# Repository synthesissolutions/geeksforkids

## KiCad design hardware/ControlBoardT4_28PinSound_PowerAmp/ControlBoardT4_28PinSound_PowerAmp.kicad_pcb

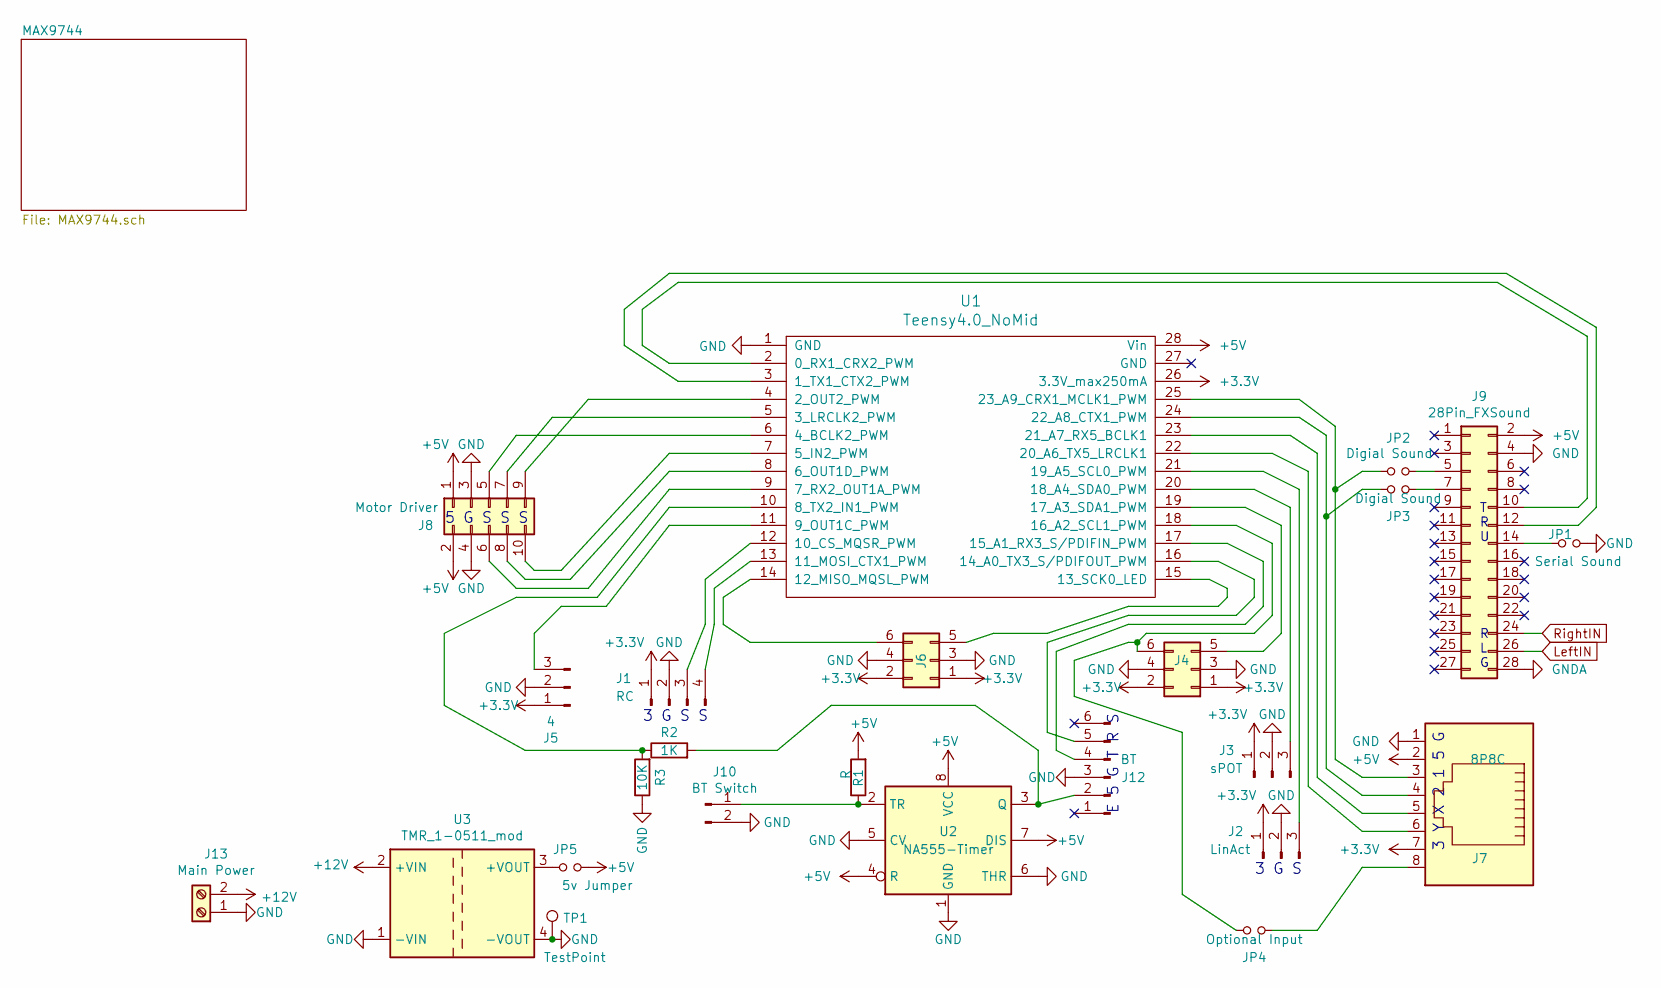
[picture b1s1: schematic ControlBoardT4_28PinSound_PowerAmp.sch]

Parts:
J1: RC; PinHeader_1x04_P2.54mm_Vertical
J2: LinAct; PinHeader_1x03_P2.54mm_Vertical
J3: sPOT; PinHeader_1x03_P2.54mm_Vertical
J4: 1 2; PinHeader_2x03_P2.54mm_Vertical
J5: 4; PinHeader_1x03_P2.54mm_Vertical
J6: 5 6; PinHeader_2x03_P2.54mm_Vertical
J7: 8P8C; RJ45_x08_Horizontal_tabs
J8: Motor Driver; PinHeader_2x05_P2.54mm_Vertical
J9: 28Pin_FXSound; FXSound_HeadPhone_2x14_P2.54mm_Short
J10: BT Switch; PinHeader_1x02_P2.54mm_Vertical
J12: BT; PinHeader_1x06_P2.54mm_Vertical
J13: Main Power; TerminalBlock_bornier-2_P5.08mm
JP1: Serial Sound; SolderJumper-2_P1.3mm_Open_TrianglePad1.0x1.5mm
JP2, JP3: Digial Sound; SolderJumper-2_P1.3mm_Open_TrianglePad1.0x1.5mm
JP4: Optional Input; SolderJumper-2_P1.3mm_Open_TrianglePad1.0x1.5mm
JP5: 5v Jumper; SolderJumper-2_P1.3mm_Open_TrianglePad1.0x1.5mm
R1: R; R_0805_2012Metric_Pad1.15x1.40mm_HandSolder
R2: 1K; R_0805_2012Metric_Pad1.15x1.40mm_HandSolder
R3: 10K; R_0805_2012Metric_Pad1.15x1.40mm_HandSolder; DigiKey ID RNCP0805FTD10K0CT-ND
TP1: TestPoint; TestPoint_Pad_1.5x1.5mm
U1: Teensy4.0_NoMid; Teensy40_NoMid
U2: NA555-Timer; DIP-8_W7.62mm
U3: TMR_1-0511_mod; Regulator_LM2596Adj

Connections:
+3V3: J1.1, J2.1, J3.1, J4.1, J4.2, J5.1, J6.1, J6.2, J7.7, U1.26 (3.3V_max250mA); also elsewhere on the board
+5V: J7.2, J8.1, J8.2, J9.2, JP5.2, R1.2, U1.28 (Vin), U2.4 (R), U2.7 (DIS), U2.8 (VCC)
+12V: J13.2, U3.2 (+VIN); also elsewhere on the board
GND: J1.2, J2.2, J3.2, J4.3, J4.4, J5.2, J6.3, J6.4, J7.1, J8.3, J8.4, J9.4, J10.2, J12.3, J13.1, JP1.2, R3.1, TP1.1, U1.1 (GND), U2.1 (GND), U2.5 (CV), U2.6 (THR), U3.1 (-VIN), U3.4 (-VOUT); also elsewhere on the board
GNDA: J9.28; also elsewhere on the board
LeftIN: J9.26; also elsewhere on the board
unnamed: J1.3, U1.12 (10_CS_MQSR_PWM)
unnamed: J1.4, U1.13 (11_MOSI_CTX1_PWM)
unnamed: J2.3, U1.21 (19_A5_SCL0_PWM)
unnamed: J3.3, U1.20 (18_A4_SDA0_PWM)
unnamed: J4.5, U1.19 (17_A3_SDA1_PWM)
unnamed: J4.6, JP4.1, U1.18 (16_A2_SCL1_PWM)
unnamed: J5.3, U1.11 (9_OUT1C_PWM)
unnamed: J6.5, U1.15 (13_SCK0_LED)
unnamed: J6.6, U1.14 (12_MISO_MQSL_PWM)
unnamed: J7.3, JP2.1, U1.25 (23_A9_CRX1_MCLK1_PWM)
unnamed: J7.4, JP3.1, U1.24 (22_A8_CTX1_PWM)
unnamed: J7.5, U1.23 (21_A7_RX5_BCLK1)
unnamed: J7.6, U1.22 (20_A6_TX5_LRCLK1)
unnamed: J7.8, JP4.2
unnamed: J8.5, U1.6 (4_BCLK2_PWM)
unnamed: J8.6, U1.9 (7_RX2_OUT1A_PWM)
unnamed: J8.7, U1.5 (3_LRCLK2_PWM)
unnamed: J8.8, U1.8 (6_OUT1D_PWM)
unnamed: J8.9, U1.4 (2_OUT2_PWM)
unnamed: J8.10, U1.7 (5_IN2_PWM)
unnamed: J9.5, JP2.2
unnamed: J9.7, JP3.2
unnamed: J9.10, U1.2 (0_RX1_CRX2_PWM)
unnamed: J9.12, U1.3 (1_TX1_CTX2_PWM)
unnamed: J9.14, JP1.1
unnamed: J10.1, R1.1, U2.2 (TR)
unnamed: J12.2, R2.2, U2.3 (Q)
unnamed: J12.4, U1.17 (15_A1_RX3_S/PDIFIN_PWM)
unnamed: J12.5, U1.16 (14_A0_TX3_S/PDIFOUT_PWM)
unnamed: JP5.1, U3.3 (+VOUT)
unnamed: R2.1, R3.2, U1.10 (8_TX2_IN1_PWM)
RightIN: J9.24; also elsewhere on the board

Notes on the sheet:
3 Y X 2 1 5 G
3 G S S
5 G S S S
3 G S
T R U
R L G
E 5 G T R S

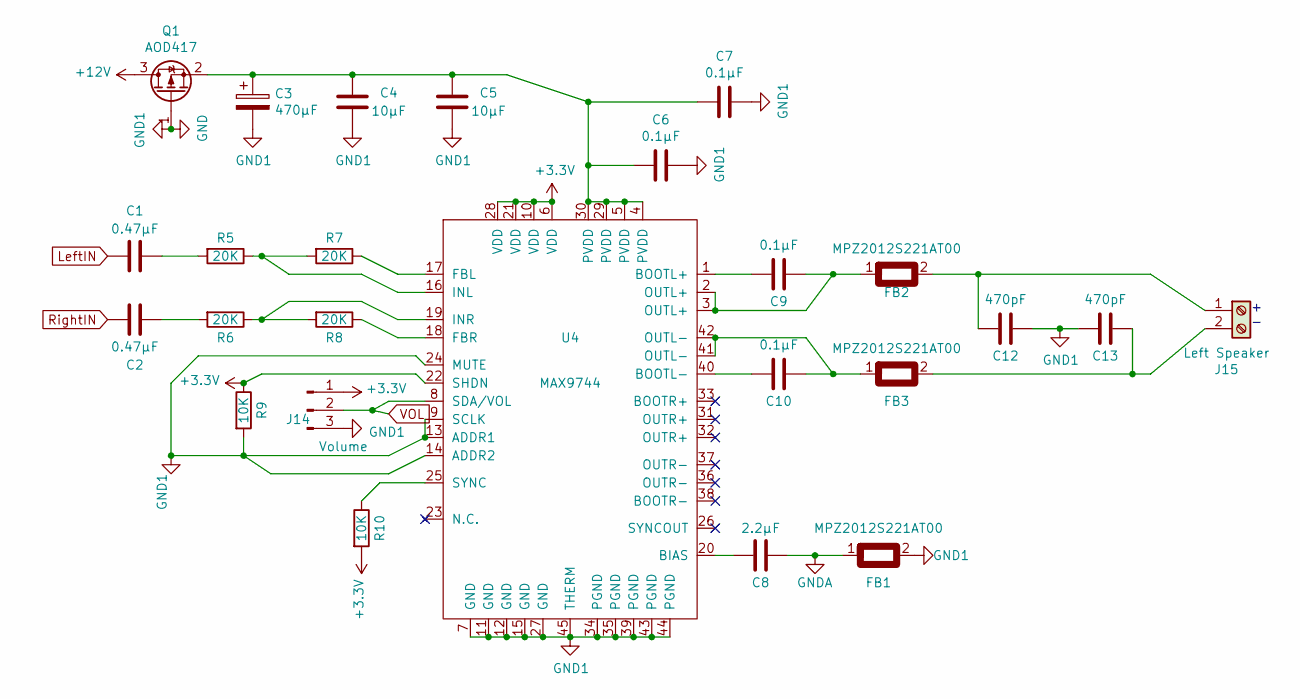
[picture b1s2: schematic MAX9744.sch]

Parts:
C1, C2: 0.47µF; C_0805_2012Metric_Pad1.15x1.40mm_HandSolder; DigiKey ID 399-8099-1-ND
C3: 470µF; CP_Radial_D8.0mm_P3.50mm; DigiKey ID 1189-1859-ND
C4, C5: 10µF; C_0805_2012Metric_Pad1.15x1.40mm_HandSolder; DigiKey ID 399-8012-1-ND
C6, C7, C9, C10: 0.1µF; C_0805_2012Metric_Pad1.15x1.40mm_HandSolder; DigiKey ID 399-8000-1-ND
C8: 2.2µF; C_0805_2012Metric_Pad1.15x1.40mm_HandSolder; DigiKey ID 399-11941-1-ND
C12, C13: 470pF; C_0805_2012Metric_Pad1.15x1.40mm_HandSolder; DigiKey ID 399-1142-1-ND
FB1, FB2, FB3: MPZ2012S221AT00; L_0805_2012Metric_Pad1.15x1.40mm_HandSolder; DigiKey ID 445-1568-1-ND
J14: Volume; JST_XH_B3B-XH-A_1x03_P2.54mm_Vertical
J15: Left Speaker; TerminalBlock_bornier-2_P5.08mm
Q1: AOD417; TO-252-2pin3D; DigiKey ID 785-1106-1-ND
R5, R6, R7, R8: 20K; R_0805_2012Metric_Pad1.15x1.40mm_HandSolder; DigiKey ID 311-20.0KCRCT-ND
R9, R10: 10K; R_0805_2012Metric_Pad1.15x1.40mm_HandSolder; DigiKey ID RNCP0805FTD10K0CT-ND
U4: MAX9744; max9744eth&plus_Mod; DigiKey ID MAX9744ETH+-ND

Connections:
+3V3: J14.1, R9.1, R10.2, U4.6 (VDD), U4.10 (VDD), U4.21 (VDD), U4.22 (SHDN), U4.28 (VDD); also elsewhere on the board
+12V: Q1.3 (D); also elsewhere on the board
GND: C3.2, C4.1, C5.1, C6.1, C7.1, C12.1, C13.2, FB1.2, J14.3, Q1.1 (G), R9.2, U4.7 (GND), U4.9 (SCLK), U4.11 (GND), U4.12 (GND), U4.13 (ADDR1), U4.14 (ADDR2), U4.15 (GND), U4.24 (MUTE), U4.27 (GND), U4.34 (PGND), U4.35 (PGND), U4.39 (PGND), U4.43 (PGND), U4.44 (PGND), U4.45 (THERM); also elsewhere on the board
GNDA: C8.2, FB1.1; also elsewhere on the board
LeftIN: C1.2; also elsewhere on the board
unnamed: C1.1, R5.2
unnamed: C2.1, R6.2
unnamed: C3.1, C4.2, C5.2, C6.2, C7.2, Q1.2 (S), U4.4 (PVDD), U4.5 (PVDD), U4.29 (PVDD), U4.30 (PVDD)
unnamed: C8.1, U4.20 (BIAS)
unnamed: C9.1, FB2.1, U4.2 (OUTL+), U4.3 (OUTL+)
unnamed: C9.2, U4.1 (BOOTL+)
unnamed: C10.1, FB3.1, U4.41 (OUTL-), U4.42 (OUTL-)
unnamed: C10.2, U4.40 (BOOTL-)
unnamed: C12.2, FB2.2, J15.1
unnamed: C13.1, FB3.2, J15.2
unnamed: J14.2, U4.8 (SDA/VOL)
unnamed: R5.1, R7.2, U4.16 (INL)
unnamed: R6.1, R8.2, U4.19 (INR)
unnamed: R7.1, U4.17 (FBL)
unnamed: R8.1, U4.18 (FBR)
unnamed: R10.1, U4.25 (SYNC)
RightIN: C2.2; also elsewhere on the board

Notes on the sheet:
+ -

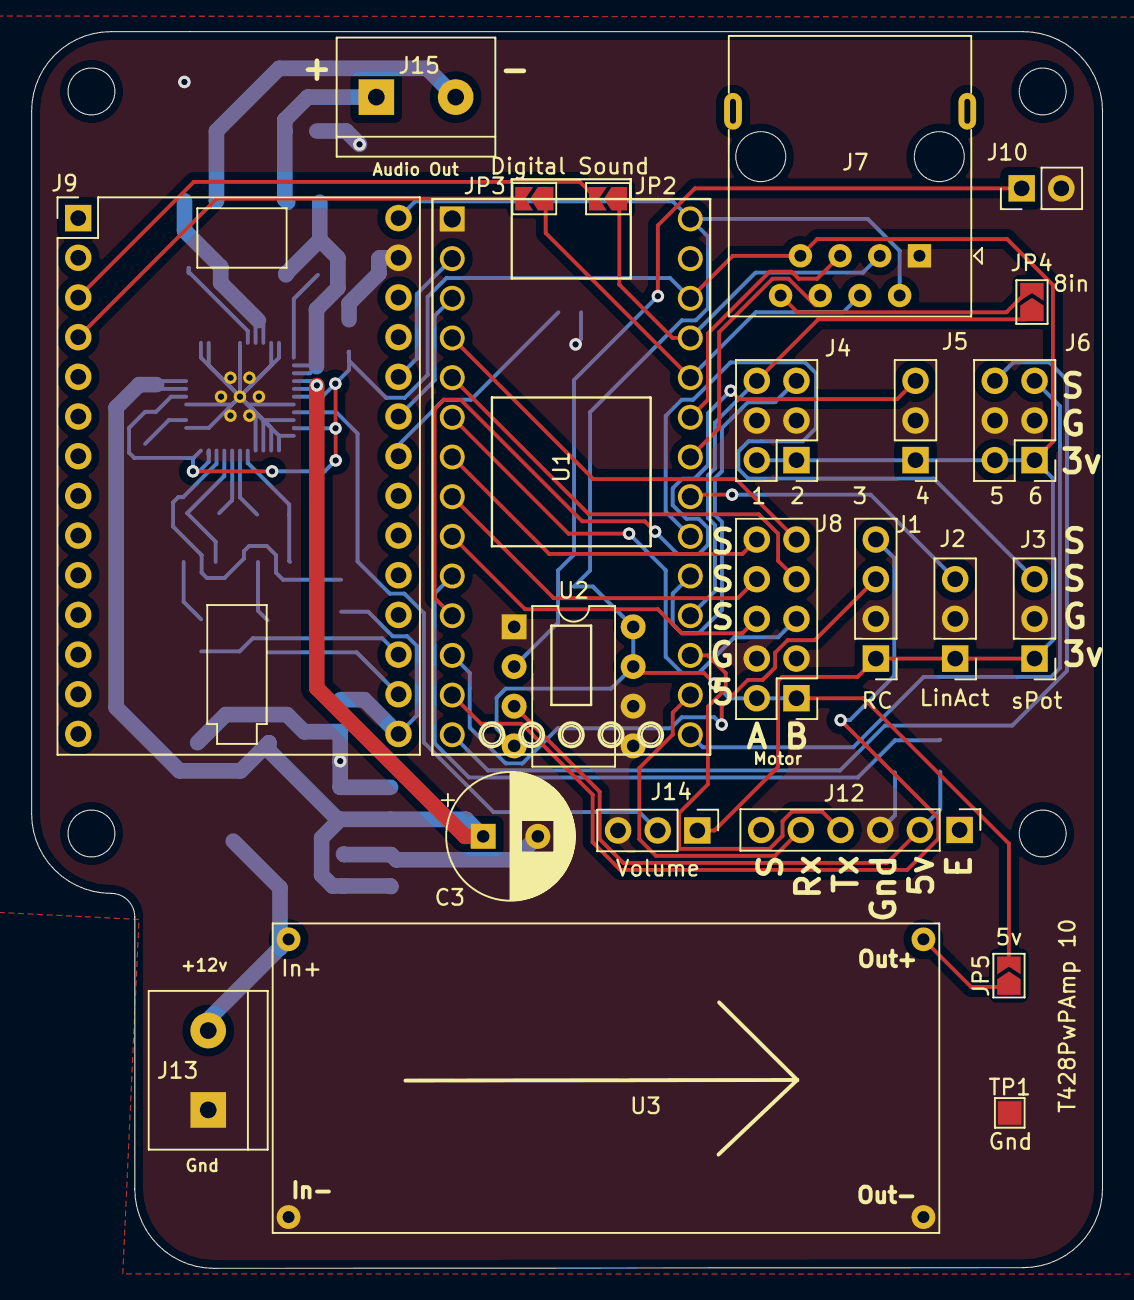
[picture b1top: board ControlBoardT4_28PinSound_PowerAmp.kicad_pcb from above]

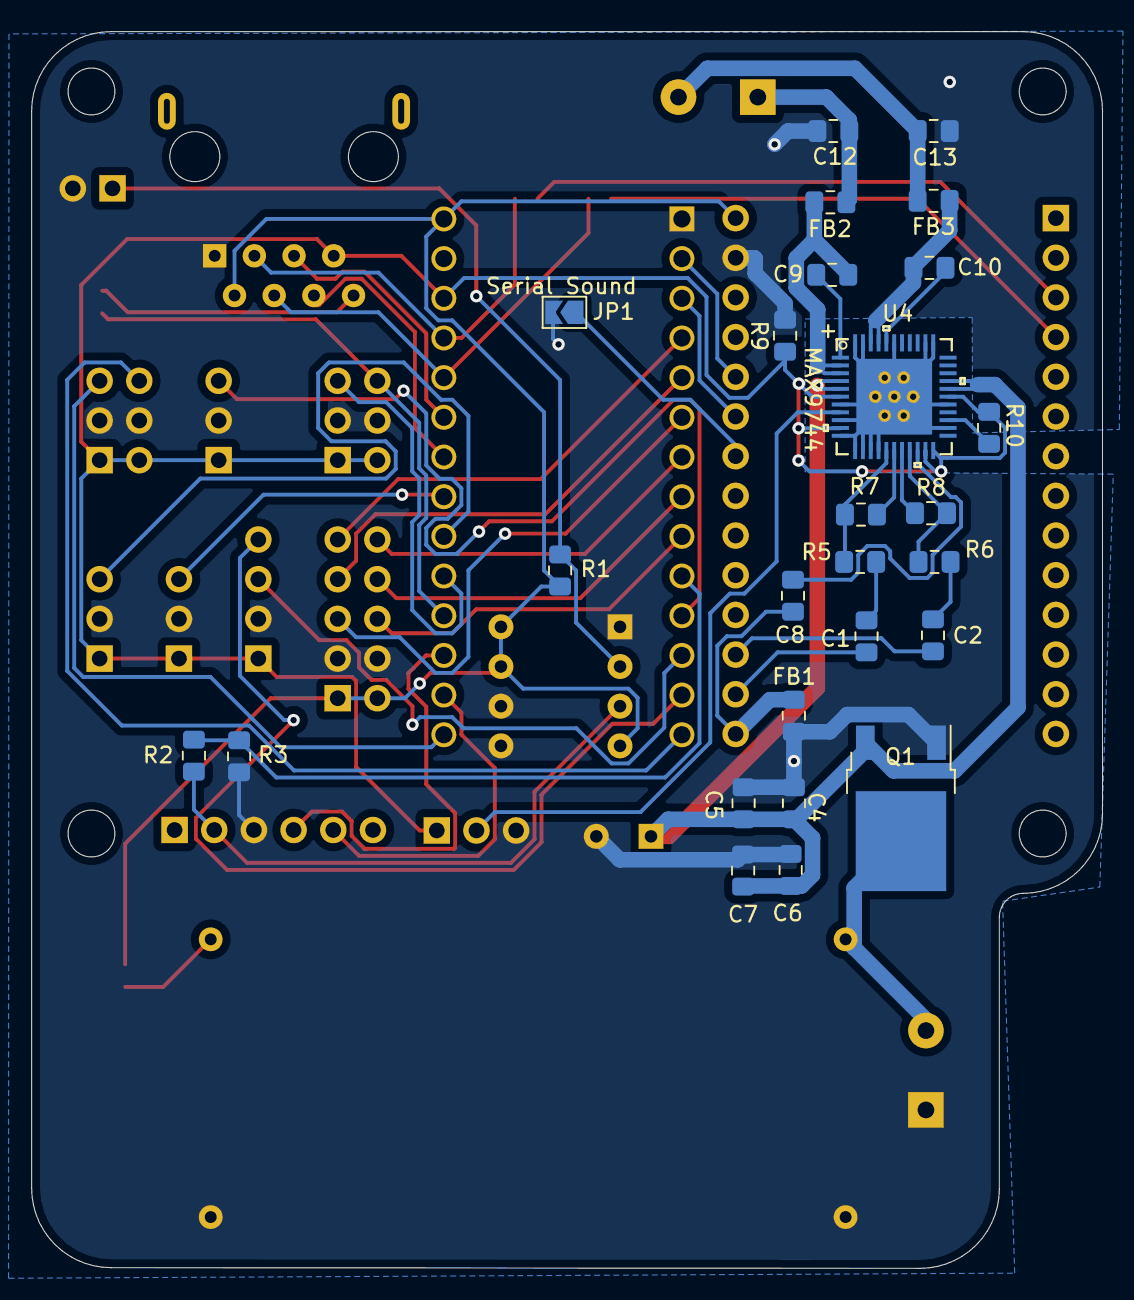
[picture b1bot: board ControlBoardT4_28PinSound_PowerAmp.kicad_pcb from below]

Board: 2 copper layers, 68.6 x 79.2 mm, 49 parts (26 on the bottom side), 54 nets.

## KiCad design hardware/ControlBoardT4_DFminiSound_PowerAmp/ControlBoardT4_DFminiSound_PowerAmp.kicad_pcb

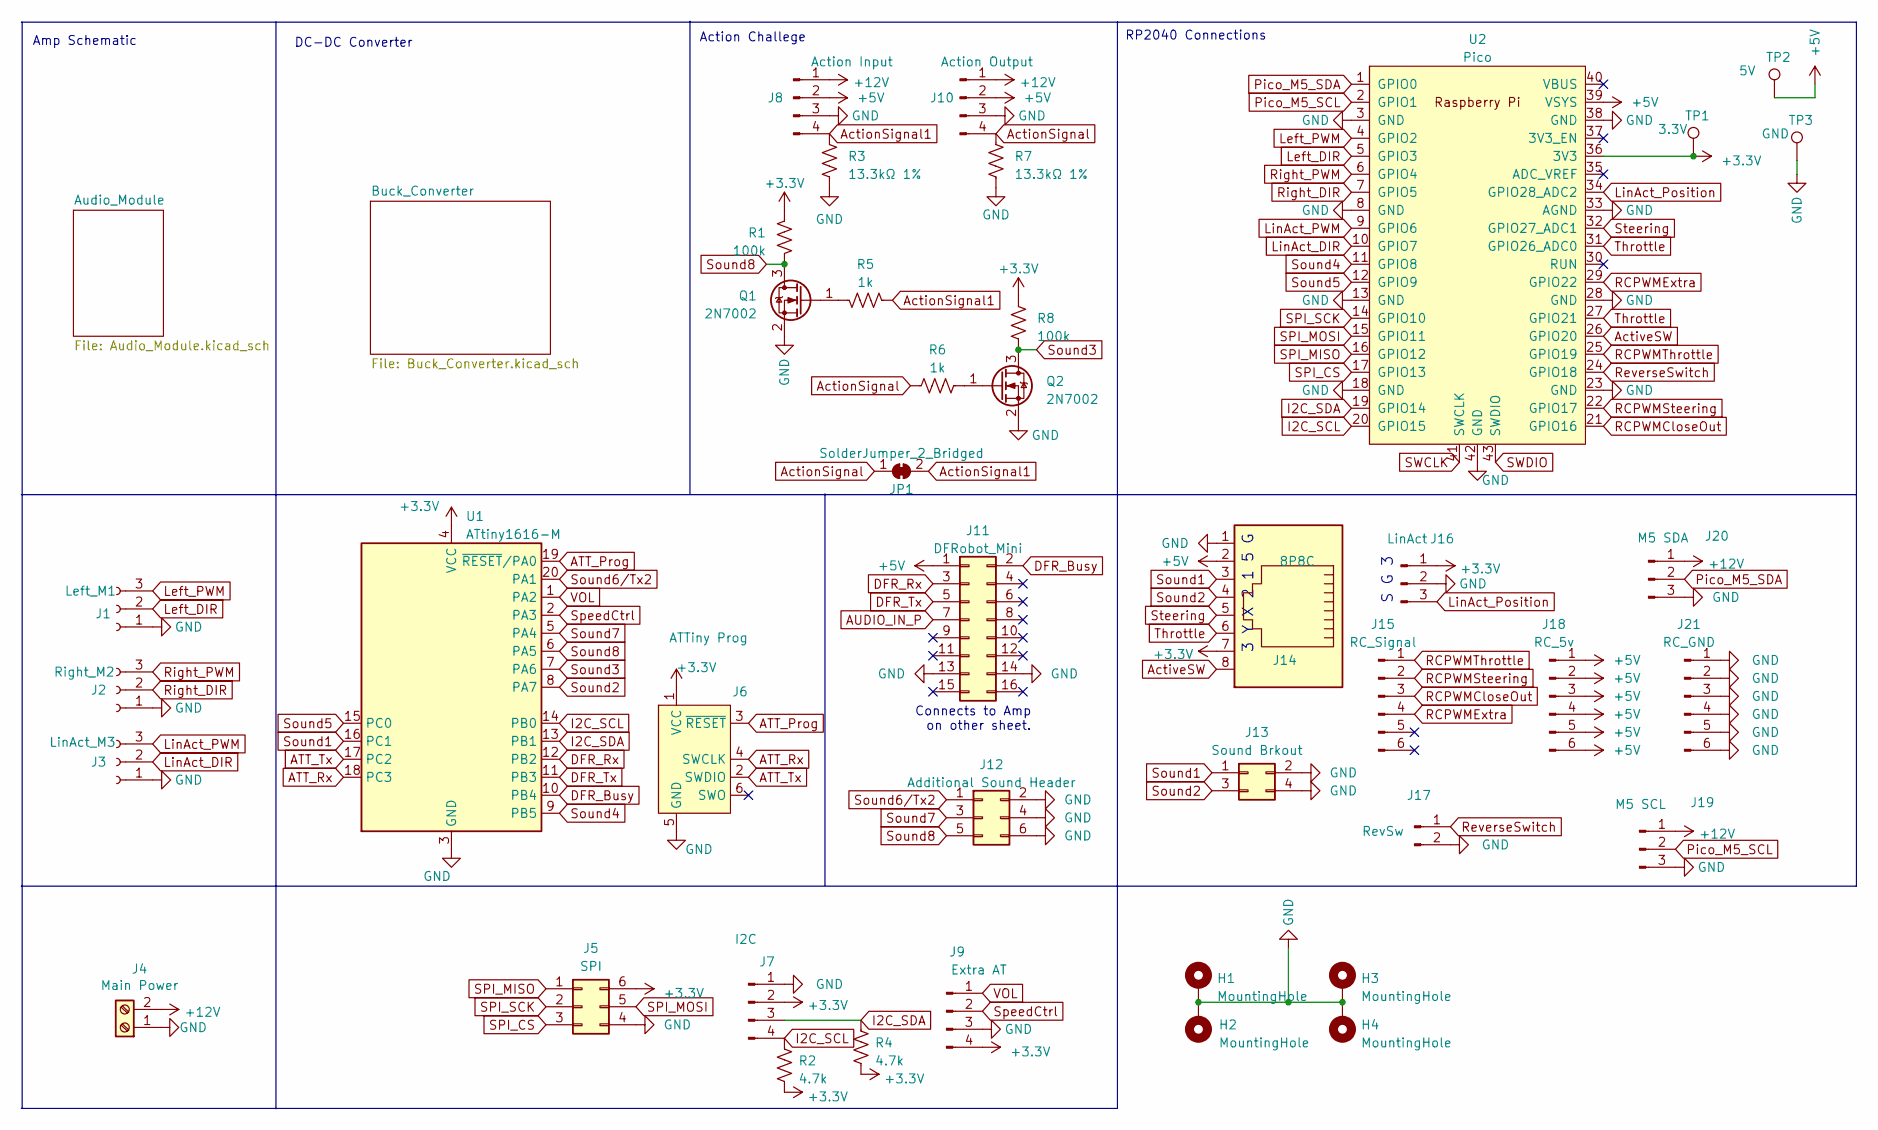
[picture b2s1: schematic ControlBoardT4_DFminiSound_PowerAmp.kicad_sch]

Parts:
H1, H2, H3, H4: MountingHole; MountingHole_2.7mm_M2.5_Pad
J1: Left_M1; PinHeader_1x03_P2.54mm_Vertical
J2: Right_M2; PinHeader_1x03_P2.54mm_Vertical
J3: LinAct_M3; PinHeader_1x03_P2.54mm_Vertical
J4: Main Power; TerminalBlock_bornier-2_P5.08mm
J5: SPI; PinHeader_2x03_P2.54mm_Vertical
J6: ATTiny Prog; Tag-Connect_TC2030-IDC-NL_2x03_P1.27mm_Vertical
J7: I2C; PinHeader_1x04_P2.54mm_Vertical
J8: Action Input; JST_XH_B4B-XH-A_1x04_P2.50mm_Vertical
J9: Extra AT; PinHeader_1x04_P2.54mm_Vertical
J10: Action Output; JST_XH_B4B-XH-A_1x04_P2.50mm_Vertical
J11: DFRobot_Mini; DFRobotMini_2x08_P2.54mm_Vertical
J12: Additional Sound Header; PinSocket_2x03_P2.54mm_Vertical
J13: Sound Brkout; PinSocket_2x02_P2.54mm_Vertical
J14: 8P8C; RJ45_x08_Tab_Up
J15: RC_Signal; PinSocket_1x06_P2.54mm_Vertical
J16: LinAct; JST_XH_B3B-XH-A_1x03_P2.54mm_Vertical
J17: RevSw; JST_XH_B2B-XH-A_1x02_P2.50mm_Vertical
J18: RC_5v; PinSocket_1x06_P2.54mm_Vertical
J19: M5 SCL; JST_XH_B3B-XH-A_1x03_P2.54mm_Vertical
J20: M5 SDA; JST_XH_B3B-XH-A_1x03_P2.54mm_Vertical
J21: RC_GND; PinSocket_1x06_P2.54mm_Vertical
JP1: SolderJumper_2_Bridged; SolderJumper-2_P1.3mm_Bridged_RoundedPad1.0x1.5mm
Q1, Q2: 2N7002; SOT-23; MPN C8545
R1, R8: 100k; R_0402_1005Metric; MPN C60491
R2, R4: 4.7k; R_0402_1005Metric; MPN C25900
R3, R7: 13.3kΩ 1%; R_0603_1608Metric; MPN C25952
R5, R6: 1k; R_0402_1005Metric; MPN C11702
TP1: 3.3V; TestPoint_Pad_1.5x1.5mm
TP2: 5V; TestPoint_Pad_1.5x1.5mm
TP3: GND; TestPoint_Pad_1.5x1.5mm
U1: ATtiny1616-M; VQFN-20-1EP_3x3mm_P0.4mm_EP1.7x1.7mm; MPN C507118
U2: Pico; RPi_Pico_SMD_TH

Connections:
+3.3V: J5.6, J6.1 (VCC), J7.2, J9.4, J14.7, J16.1, R1.1, R2.1, R4.1, R8.1, TP1.1, U1.4 (VCC), U2.36 (3V3)
+5V: J8.2, J10.2, J11.1, J14.2, J18.1, J18.2, J18.3, J18.4, J18.5, J18.6, TP2.1, U2.39 (VSYS); also elsewhere on the board
+12V: J4.2, J8.1, J10.1, J19.1, J20.1; also elsewhere on the board
ATT_Prog: J6.3 (~RESET), U1.19 (~RESET/PA0)
ATT_Rx: J6.4 (SWCLK), U1.18 (PC3)
ATT_Tx: J6.2 (SWDIO), U1.17 (PC2)
AUDIO_IN_P: J11.7; also elsewhere on the board
ActionSignal: J10.4, JP1.1 (A), R6.1, R7.1
ActionSignal1: J8.4, JP1.2 (B), R3.1, R5.1
ActiveSW: J14.8, U2.26 (GPIO20)
DFR_Busy: J11.2, U1.10 (PB4)
DFR_Rx: J11.3, U1.12 (PB2)
DFR_Tx: J11.5, U1.11 (PB3)
GND: H1.1, H2.1, H3.1, H4.1, J1.1, J2.1, J3.1, J4.1, J5.4, J6.5 (GND), J7.1, J8.3, J9.3, J10.3, J11.13, J11.14, J12.2, J12.4, J12.6, J13.2, J13.4, J14.1, J16.2, J17.2, J19.3, J20.3, J21.1, J21.2, J21.3, J21.4, J21.5, J21.6, Q1.2 (S), Q2.2 (S), R3.2, R7.2, TP3.1, U1.3 (GND), U1.21 (GND), U2.3 (GND), U2.8 (GND), U2.13 (GND), U2.18 (GND), U2.23 (GND), U2.28 (GND), U2.33 (AGND), U2.38 (GND), U2.42 (GND); also elsewhere on the board
I2C_SCL: J7.4, R2.2, U1.14 (PB0), U2.20 (GPIO15)
I2C_SDA: J7.3, R4.2, U1.13 (PB1), U2.19 (GPIO14)
Left_DIR: J1.2, U2.5 (GPIO3)
Left_PWM: J1.3, U2.4 (GPIO2)
LinAct_DIR: J3.2, U2.10 (GPIO7)
LinAct_PWM: J3.3, U2.9 (GPIO6)
LinAct_Position: J16.3, U2.34 (GPIO28_ADC2)
unnamed: Q1.1 (G), R5.2
unnamed: Q2.1 (G), R6.2
Pico_M5_SCL: J19.2, U2.2 (GPIO1)
Pico_M5_SDA: J20.2, U2.1 (GPIO0)
RCPWMCloseOut: J15.3, U2.21 (GPIO16)
RCPWMExtra: J15.4, U2.29 (GPIO22)
RCPWMSteering: J15.2, U2.22 (GPIO17)
RCPWMThrottle: J15.1, U2.25 (GPIO19)
ReverseSwitch: J17.1, U2.24 (GPIO18)
Right_DIR: J2.2, U2.7 (GPIO5)
Right_PWM: J2.3, U2.6 (GPIO4)
SPI_CS: J5.3, U2.17 (GPIO13)
SPI_MISO: J5.1, U2.16 (GPIO12)
SPI_MOSI: J5.5, U2.15 (GPIO11)
SPI_SCK: J5.2, U2.14 (GPIO10)
SWCLK: U2.41 (SWCLK)
SWDIO: U2.43 (SWDIO)
Sound1: J13.1, J14.3, U1.16 (PC1)
Sound2: J13.3, J14.4, U1.8 (PA7)
Sound3: Q2.3 (D), R8.2, U1.7 (PA6)
Sound4: U1.9 (PB5), U2.11 (GPIO8)
Sound5: U1.15 (PC0), U2.12 (GPIO9)
Sound6/Tx2: J12.1, U1.20 (PA1)
Sound7: J12.3, U1.5 (PA4)
Sound8: J12.5, Q1.3 (D), R1.2, U1.6 (PA5)
SpeedCtrl: J9.2, U1.2 (PA3)
Steering: J14.5, U2.32 (GPIO27_ADC1)
Throttle: J14.6, U2.27 (GPIO21), U2.31 (GPIO26_ADC0)
VOL: J9.1, U1.1 (PA2)

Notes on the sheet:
Connects to Amp on other sheet.
3 Y X 2 1 5 G
RP2040 Connections
Amp Schematic
DC-DC Converter
Action Challege
S G 3

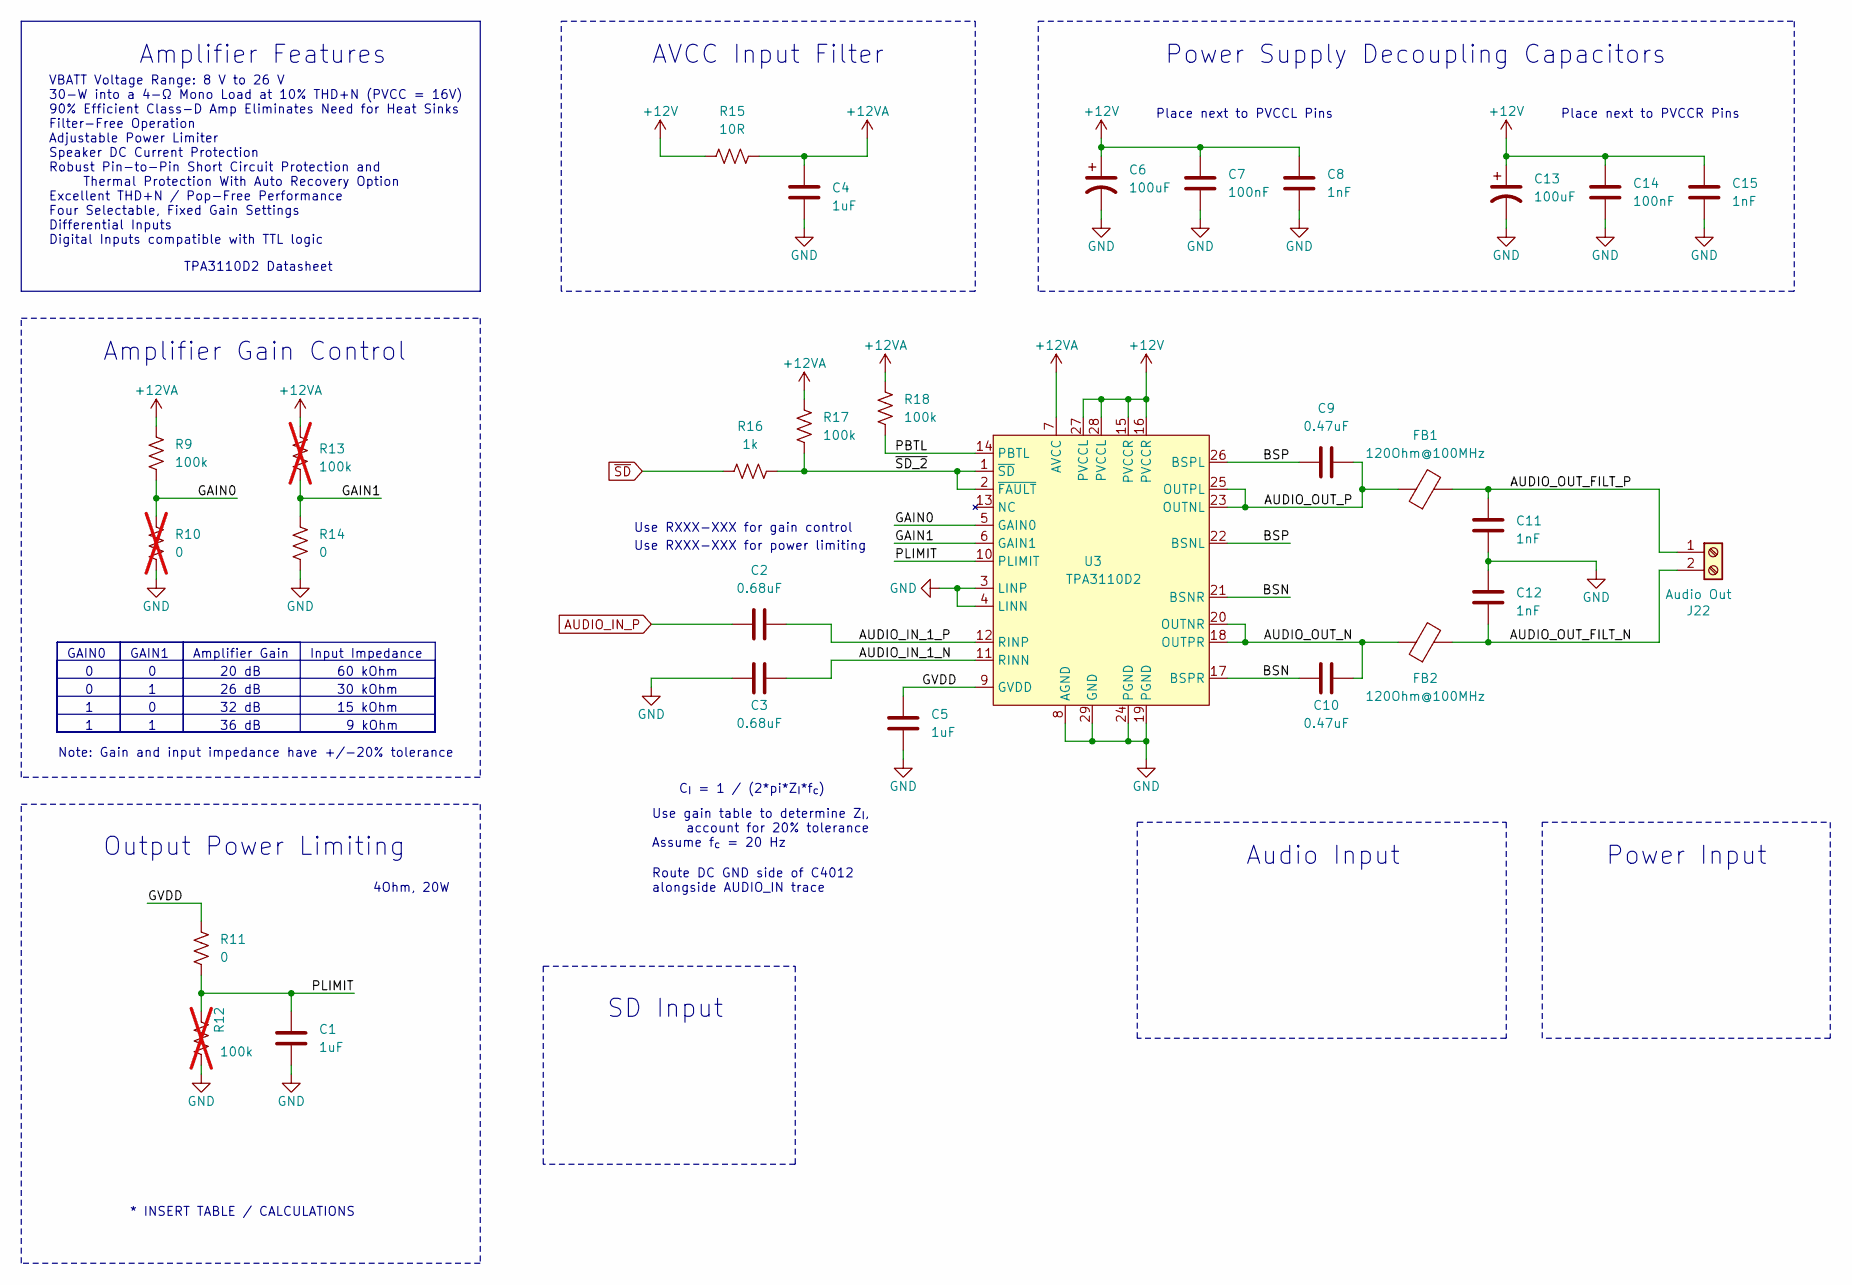
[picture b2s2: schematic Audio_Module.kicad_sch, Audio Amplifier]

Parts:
C1, C4, C5: 1uF; C_0402_1005Metric; MPN C1518208
C2, C3: 0.68uF; C_0402_1005Metric; MPN C113784
C6, C13: 100uF; CP_Radial_D8.0mm_P3.50mm; MPN C112510
C7, C14: 100nF; C_0402_1005Metric; MPN C105882
C8, C11, C12, C15: 1nF; C_0402_1005Metric; MPN C106205
C9, C10: 0.47uF; C_0402_1005Metric; MPN C437527
FB1, FB2: 120Ohm@100MHz; L_1206_3216Metric; MPN C3011219
J22: Audio Out; TerminalBlock_bornier-2_P5.08mm
R9, R17, R18: 100k; R_0402_1005Metric; MPN C60491
R10: 0; R_0402_1005Metric; MPN C17168; not fitted
R11, R14: 0; R_0402_1005Metric; MPN C17168
R12, R13: 100k; R_0402_1005Metric; MPN C60491; not fitted
R15: 10R; R_0603_1608Metric; MPN C22859
R16: 1k; R_0402_1005Metric; MPN C11702
U3: TPA3110D2; HTSSOP-28-1EP_4.4x9.7mm_P0.65mm_EP3.4x9.5mm_Mask2.4x6.17mm_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; MPN C30132

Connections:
+12V: C6.1, C7.1, C8.1, C13.1, C14.1, C15.1, R15.1, U3.15 (PVCCR), U3.16 (PVCCR), U3.27 (PVCCL), U3.28 (PVCCL); also elsewhere on the board
+12VA: C4.1, R9.1, R13.1, R15.2, R17.1, R18.1, U3.7 (AVCC)
/Audio_Module/AUDIO_IN_1_N: C3.1, U3.11 (RINN)
/Audio_Module/AUDIO_IN_1_P: C2.2, U3.12 (RINP)
/Audio_Module/AUDIO_OUT_FILT_N: C12.2, FB2.2, J22.2
/Audio_Module/AUDIO_OUT_FILT_P: C11.1, FB1.2, J22.1
/Audio_Module/AUDIO_OUT_N: C10.1, FB2.1, U3.18 (OUTPR), U3.20 (OUTNR)
/Audio_Module/AUDIO_OUT_P: C9.1, FB1.1, U3.23 (OUTNL), U3.25 (OUTPL)
/Audio_Module/BSN: C10.2, U3.17 (BSPR), U3.21 (BSNR)
/Audio_Module/BSP: C9.2, U3.22 (BSNL), U3.26 (BSPL)
/Audio_Module/GAIN0: R9.2, R10.1, U3.5 (GAIN0)
/Audio_Module/GAIN1: R13.2, R14.1, U3.6 (GAIN1)
/Audio_Module/GVDD: C5.1, R11.1, U3.9 (GVDD)
/Audio_Module/PBTL: R18.2, U3.14 (PBTL)
/Audio_Module/PLIMIT: C1.1, R11.2, R12.1, U3.10 (PLIMIT)
/Audio_Module/~SD_2: R16.2, R17.2, U3.1 (~SD), U3.2 (~FAULT)
AUDIO_IN_P: C2.1; also elsewhere on the board
GND: C1.2, C3.2, C4.2, C5.2, C6.2, C7.2, C8.2, C11.2, C12.1, C13.2, C14.2, C15.2, R10.2, R12.2, R14.2, U3.3 (LINP), U3.4 (LINN), U3.8 (AGND), U3.19 (PGND), U3.24 (PGND), U3.29 (GND); also elsewhere on the board
~SD: R16.1

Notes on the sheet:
30 kOhm
Route DC GND side of C4012 alongside AUDIO_IN trace
Use gain table to determine Z_{I}, account for 20% tolerance Assume f_{c} = 20 Hz
Use RXXX-XXX for power limiting
Amplifier Gain Control
GAIN0
Output Power Limiting
32 dB
C_{I} = 1 / (2*pi*Z_{I}*f_{c})
Use RXXX-XXX for gain control
20 dB
* INSERT TABLE / CALCULATIONS
SD Input
Audio Input
Note: Gain and input impedance have +/-20% tolerance
26 dB
VBATT Voltage Range: 8 V to 26 V 30-W into a 4-Ω Mono Load at 10% THD+N (PVCC = 16V) 90% Efficient Class-D Amp Eliminates Need for Heat Sinks Filter-Free Operation Adjustable Power Limiter Speaker DC Current Protection Robust Pin-to-Pin Short Circuit Protection and Thermal Protection With Auto Reco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
Amplifier Features
Amplifier Gain
Power Input
36 dB
4Ohm, 20W
TPA3110D2 Datasheet
AVCC Input Filter
15 kOhm
9 kOhm
Place next to PVCCR Pins
GAIN1
60 kOhm
Input Impedance
Power Supply Decoupling Capacitors
Place next to PVCCL Pins

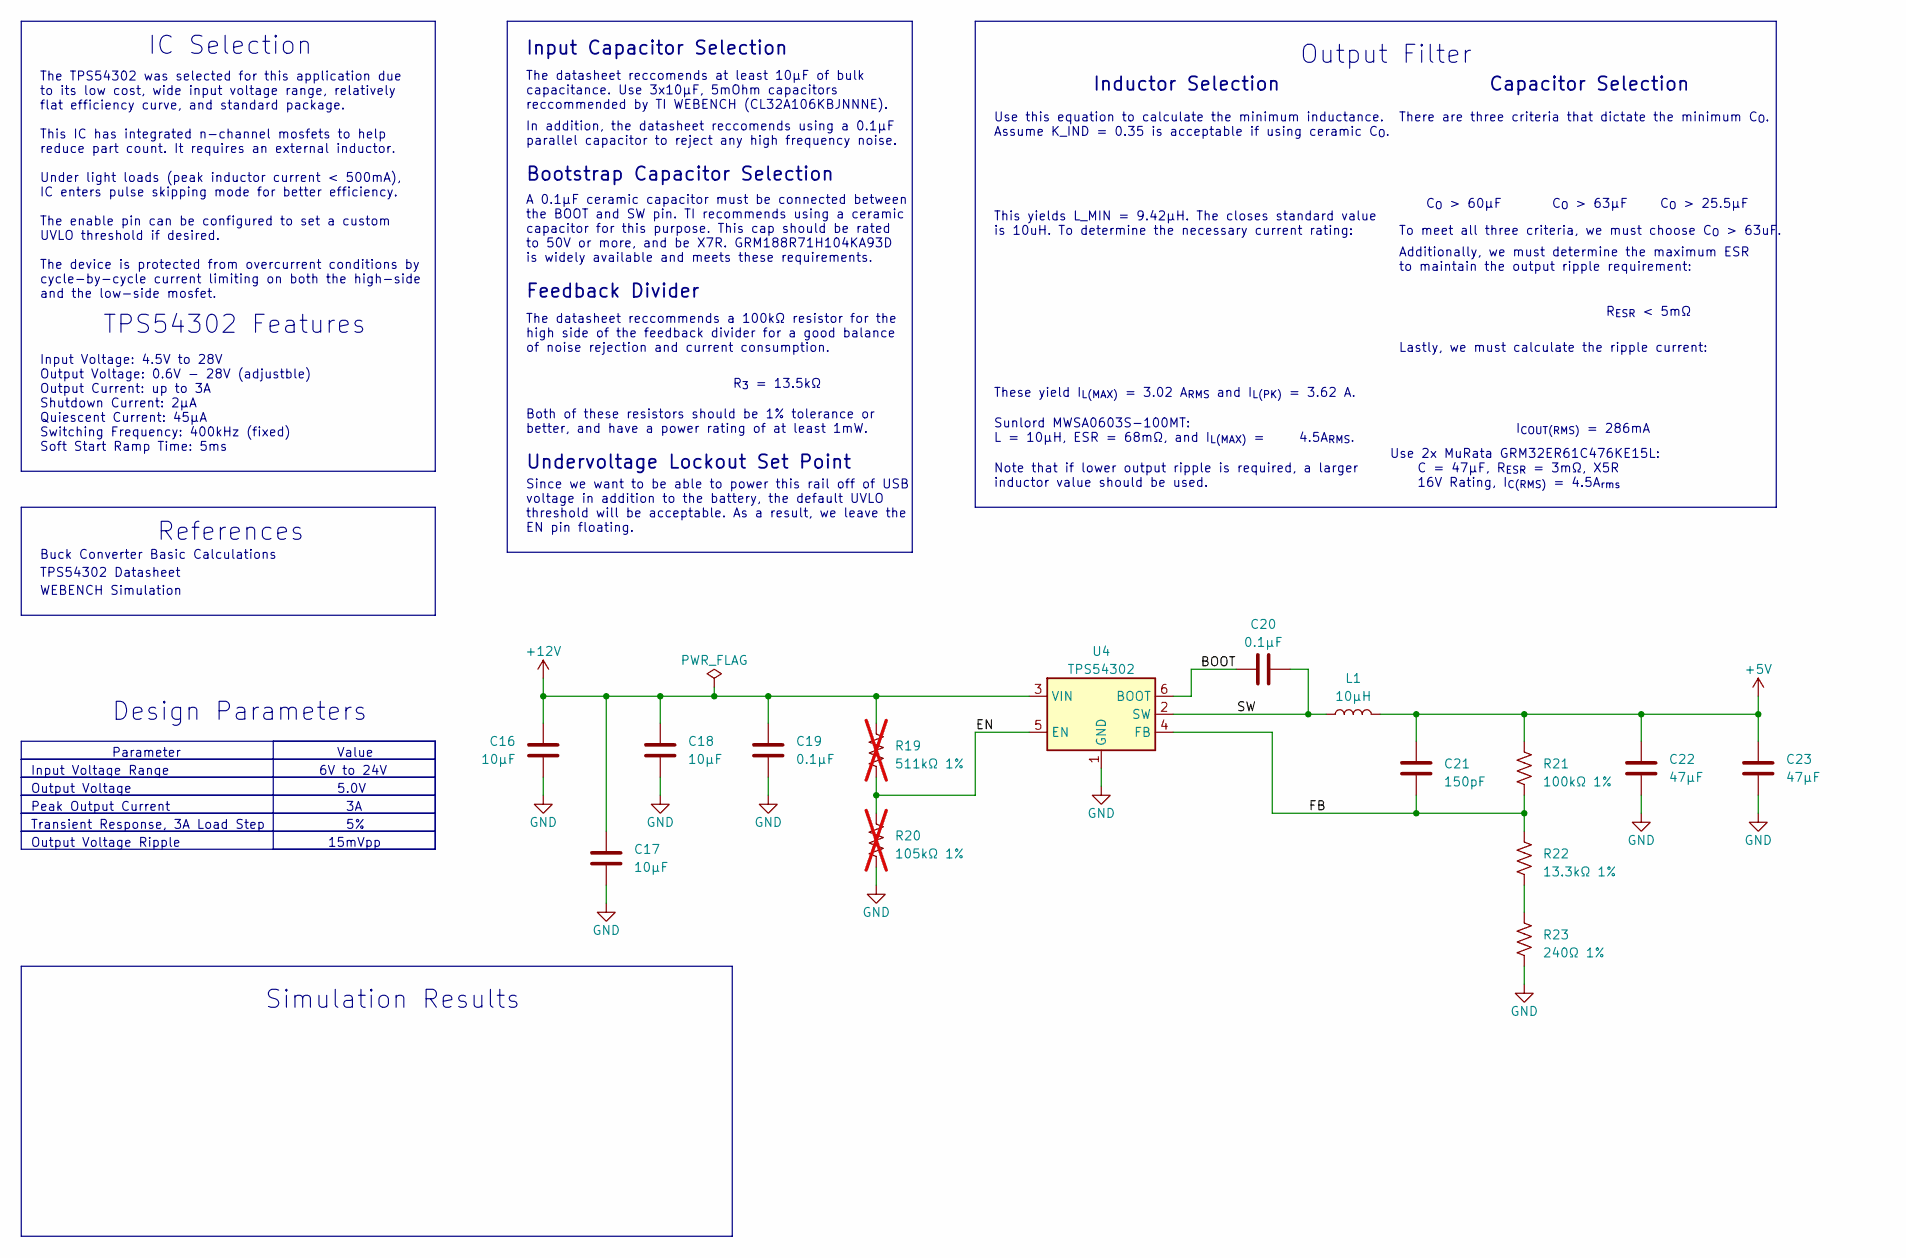
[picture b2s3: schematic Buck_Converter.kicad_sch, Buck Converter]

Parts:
C16, C17, C18: 10µF; C_1210_3225Metric; MPN C380537
C19, C20: 0.1µF; C_0603_1608Metric; MPN C77055
C21: 150pF; C_0603_1608Metric; MPN C527999
C22, C23: 47µF; C_1210_3225Metric; MPN C77101
L1: 10µH; L_Sunlord_MWSA0603S; MPN C132141
R19: 511kΩ 1%; R_0603_1608Metric; MPN C23194; not fitted
R20: 105kΩ 1%; R_0603_1608Metric; MPN C16840; not fitted
R21: 100kΩ 1%; R_0603_1608Metric; MPN C25803
R22: 13.3kΩ 1%; R_0603_1608Metric; MPN C25952
R23: 240Ω 1%; R_0603_1608Metric; MPN C23350
U4: TPS54302; SOT-23-6; MPN C311983

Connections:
+5V: C21.1, C22.1, C23.1, L1.2, R21.1; also elsewhere on the board
+12V: C16.1, C17.1, C18.1, C19.1, R19.1, U4.3 (VIN); also elsewhere on the board
/Buck_Converter/BOOT: C20.1, U4.6 (BOOT)
/Buck_Converter/EN: R19.2, R20.1, U4.5 (EN)
/Buck_Converter/FB: C21.2, R21.2, R22.1, U4.4 (FB)
/Buck_Converter/SW: C20.2, L1.1, U4.2 (SW)
GND: C16.2, C17.2, C18.2, C19.2, C22.2, C23.2, R20.2, R23.2, U4.1 (GND); also elsewhere on the board
unnamed: R22.2, R23.1

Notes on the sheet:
C_{O} > 60µF
Sunlord MWSA0603S-100MT: L = 10µH, ESR = 68mΩ, and I_{L(MAX)} = 4.5A_{RMS}.
R_{ESR} < 5mΩ
Inductor Selection
Output Voltage
These yield I_{L(MAX)} = 3.02 A_{RMS} and I_{L(PK)} = 3.62 A.
Output Voltage Ripple
In addition, the datasheet reccomends using a 0.1µF parallel capacitor to reject any high frequency noise.
Note that if lower output ripple is required, a larger inductor value should be used.
The TPS54302 was selected for this application due to its low cost, wide input voltage range, relatively flat efficiency curve, and standard package. This IC has integrated n-channel mosfets to help reduce part count. It requires an external inductor. Under light loads (peak inductor current < 500m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
IC Selection
Undervoltage Lockout Set Point
Input Voltage Range
This yields L_MIN = 9.42µH. The closes standard value is 10uH. To determine the necessary current rating:
TPS54302 Features
Since we want to be able to power this rail off of USB voltage in addition to the battery, the default UVLO threshold will be acceptable. As a result, we leave the EN pin floating.
15mVpp
The datasheet reccommends a 100kΩ resistor for the high side of the feedback divider for a good balance of noise rejection and current consumption.
Use 2x MuRata GRM32ER61C476KE15L: C = 47µF, R_{ESR} = 3mΩ, X5R 16V Rating, I_{C(RMS)} = 4.5A_{rms}
Capacitor Selection
The datasheet reccomends at least 10µF of bulk capacitance. Use 3x10µF, 5mOhm capacitors reccommended by TI WEBENCH (CL32A106KBJNNNE).
Feedback Divider
Simulation Results
References
Output Filter
WEBENCH Simulation
Buck Converter Basic Calculations
6V to 24V
Use this equation to calculate the minimum inductance. Assume K_IND = 0.35 is acceptable if using ceramic C_{O}.
Input Capacitor Selection
Design Parameters
There are three criteria that dictate the minimum C_{O}.
Parameter
5.0V
R_{3} = 13.5kΩ
C_{O} > 25.5µF
To meet all three criteria, we must choose C_{O} > 63uF.
Additionally, we must determine the maximum ESR to maintain the output ripple requirement:
I_{COUT(RMS)} = 286mA
Bootstrap Capacitor Selection

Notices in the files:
parts and their libraries:
Copyright 2021 Accelerated Designs. All rights reserved.
